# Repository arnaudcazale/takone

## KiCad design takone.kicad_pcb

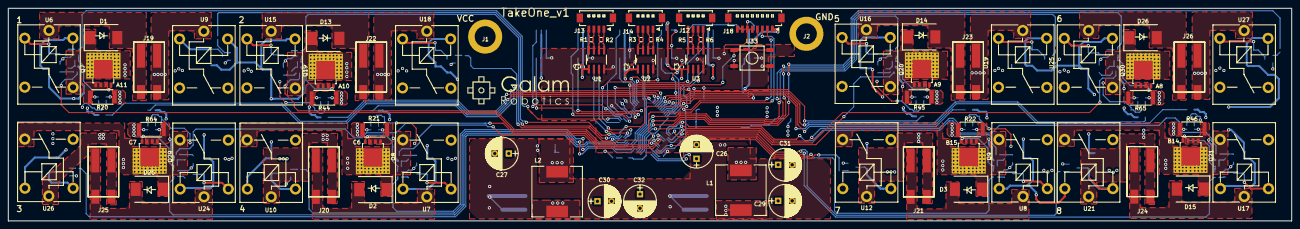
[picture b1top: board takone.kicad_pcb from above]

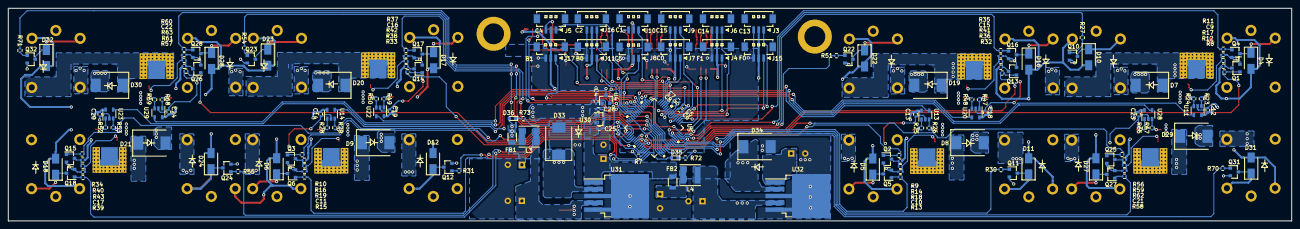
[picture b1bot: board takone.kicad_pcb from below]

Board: 4 copper layers, 320.0 x 53.0 mm, 238 parts (163 on the bottom side), 187 nets.

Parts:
C1, C2, C3, C6, C8, C12, C13, C14, C18, C19, C20, C23, C24, C25, C28: 100n; C_0402
C4: 0.47u; C_0402
C5: 1u; C_0402
C7: 4.7u; C_0402
C9, C10, C11, C15, C16, C17, C21, C22: DNP; C_0402
C26, C27, C31, C32: 100u; CP_Radial_D8.0mm_P3.50mm
C29, C30: 330u; CP_Radial_D8.0mm_P3.50mm
D1, D2, D3, D7, D8, D9, D13, D14, D15, D19, D20, D21, D25, D26, D29, D30: S10JC; D_SMC
D4, D5, D6, D10, D11, D12, D16, D17, D18, D22, D23, D24, D27, D28, D31, D32: M1; D_SMA
D33, D34: SS3H10; D_SMC
D35, D36: LED; LED_0603
FB1, FB2: Ferrite_Bead; R_1206
J1, J2: Conn_01x01; hole
J3, J4, J5, J6, J7, J8, J9, J10, J11, J15, J16, J17: Conn_01x03; Hirose_DF13C-03P-1.25V_03x1.25mm_Straight
J12, J13, J14: Conn_01x04; Hirose_DF13C-04P-1.25V_04x1.25mm_Straight
J18: Conn_01x08; Hirose_DF13C-08P-1.25V_08x1.25mm_Straight
J19, J20, J21, J22, J23, J24, J25, J26: Conn_02x02_Counter_Clockwise; P-2060-402998-404
L1: 220uH; L_12x12mm_h8mm
L2: 1mH; L_12x12mm_h8mm
L3, L4: 20u; L_Taiyo-Yuden_MD-5050
Q1, Q2, Q3, Q4, Q5, Q6, Q10, Q11, Q12, Q13, Q14, Q15, Q16, Q17, Q18, Q22, Q23, Q24, Q25, Q26, Q27, Q28, Q31, Q32: SS8050; SOT-23
Q7, Q8, Q9, Q19, Q20, Q21, Q29, Q30: PSMN028-100YS; LFPAK56_ThermalVias-1
R1, R2, R3, R4, R5, R6: 120; R_0402
R7, R12, R14, R16, R36, R38, R40, R59, R61: 10k; R_0402
R8, R9, R10, R11, R13, R15, R27, R30, R31, R32, R33, R34, R35, R37, R39, R51, R54, R55, R56, R57, R58, R60, R70, R71: 680R; R_0402
R17, R18, R19, R41, R42, R43, R62, R63: 1; R_0402
R20, R21, R22, R44, R45, R46, R64, R65: 0.05; R_2512
R23, R24, R25, R26, R28, R29, R47, R48, R49, R50, R52, R53, R66, R67, R68, R69: 0; R_0402
R72, R73: 330R; R_0402
U1, U2, U3: R_8; ADM3488ARZ
U4: REF2925; SOT-23
U5: LQFP-64; STM32G0_LQFP64_T1
U6, U7, U8, U9, U10, U12, U15, U16, U17, U18, U19, U21, U24, U25, U26, U27: Relay; Relay_SPDT_SANYOU_SRD_Series_Form_C
U11, U13, U14, U20, U22, U23, U28, U29: INA180; SOT-23-5
U30: TLV760; SOT-23
U31, U32: TL2575HV; TO-263-5_TabPin3
U33: switch

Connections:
+3.3V(ANALOG): C4.1, C12.2, C13.2, C14.2, C18.2, C19.2, C20.2, C23.2, C24.2, C28.1, U4.1, U11.5, U13.5, U14.5, U20.5, U22.5, U23.5, U28.5, U29.5, U30.1
+3.3V(DIG): C1.1, C2.1, C3.1, C7.1, C8.1, D36.2, FB1.1, J3.2, J4.2, J5.2, J6.2, J7.2, J8.2, J9.2, J10.2, J11.2, J15.2, J16.2, J17.2, J18.1, U1.1, U2.1, U3.1, U5.6, U5.8
+12V: C25.1, C26.1, D4.2, D5.2, D6.2, D10.2, D11.2, D12.2, D16.2, D17.2, D18.2, D22.2, D23.2, D24.2, D27.2, D28.2, D31.2, D32.2, FB2.1, R12.1, R14.1, R16.1, R36.1, R38.1, R40.1, R59.1, R61.1, U6.4, U7.4, U8.4, U9.4, U10.4, U12.4, U15.4, U16.4, U17.4, U18.4, U19.4, U21.4, U24.4, U25.4, U26.4, U27.4, U30.2, U31.1
+48V: C27.1, J1.1, U6.2, U7.2, U8.2, U9.2, U10.2, U12.2, U15.2, U16.2, U17.2, U18.2, U19.2, U21.2, U24.2, U25.2, U26.2, U27.2, U32.1
/command/NRST: J18.4, U5.12, U33.1, U33.2
/command/RX1: U1.2, U5.61
/command/RX2: U2.2, U5.56
/command/RX3: U3.2, U5.1
/command/SWCLK: J18.3, R7.1, U5.46
/command/SWDIO: J18.2, U5.45
/command/TX1: U1.3, U5.60
/command/TX2: U2.3, U5.55
/command/TX3: U3.3, U5.64
/command/encoder1: J3.1, U5.3
/command/encoder2: J6.1, U5.4
/command/encoder3: J9.1, U5.5
/command/encoder4: J15.1, U5.10
/command/encoder5: J4.1, U5.11
/command/encoder6: J7.1, U5.13
/command/encoder7: J10.1, U5.14
/command/encoder8: J16.1, U5.15
/command/spare1: J5.1, U5.25
/command/spare2: J8.1, U5.26
/command/spare3: J11.1, U5.27
/command/spare4: J17.1, U5.28
GND: C9.2, C10.2, C11.2, C15.2, C16.2, C17.2, C21.2, C22.2, C25.2, C26.2, C27.2, C28.2, C29.2, C30.2, C31.2, C32.2, D33.2, D34.2, Q1.2, Q2.2, Q3.2, Q4.2, Q5.2, Q6.2, Q10.2, Q11.2, Q12.2, Q13.2, Q14.2, Q15.2, Q16.2, Q17.2, Q18.2, Q22.2, Q23.2, Q24.2, Q25.2, Q26.2, Q27.2, Q28.2, Q31.2, Q32.2, R73.2, U30.3, U31.3, U31.5, U32.3, U32.5
GNDA: C12.1, C13.1, C14.1, C18.1, C19.1, C20.1, C23.1, C24.1, U11.2, U13.2, U14.2, U20.2, U22.2, U23.2, U28.2, U29.2
GNDD: C1.2, C2.2, C3.2, C4.2, C5.2, C6.2, C7.2, C8.2, J3.3, J4.3, J5.3, J6.3, J7.3, J8.3, J9.3, J10.3, J11.3, J15.3, J16.3, J17.3, J18.5, J18.6, J18.7, J18.8, R7.2, R72.2, U1.4, U2.4, U3.4, U4.3, U5.9, U33.3, U33.4
GNDPWR: R20.1, R21.1, R22.1, R24.1, R26.1, R29.1, R44.1, R45.1, R46.1, R48.1, R50.1, R53.1, R64.1, R65.1, R67.1, R69.1
MOS1: R8.1, U5.43
MOS2: R32.1, U5.42
MOS3: R56.1, U5.39
MOS4: R9.1, U5.38
MOS5: R33.1, U5.37
MOS6: R57.1, U5.36
MOS7: R10.1, U5.35
MOS8: R34.1, U5.34
unnamed: C5.1, C6.1, U4.2, U5.7
unnamed: C9.1, Q7.4, R17.2
unnamed: C10.1, Q8.4, R18.2
unnamed: C11.1, Q9.4, R19.2
unnamed: C15.1, Q19.4, R41.2
unnamed: C16.1, Q20.4, R42.2
unnamed: C17.1, Q21.4, R43.2
unnamed: C21.1, Q29.4, R62.2
unnamed: C22.1, Q30.4, R63.2
unnamed: C29.1, L1.2, L3.1, U31.4
unnamed: C30.1, L2.2, L4.1, U32.4
unnamed: C31.1, FB1.2, L3.2
unnamed: C32.1, FB2.2, L4.2
unnamed: D1.1, D7.1, Q7.5, U6.3, U9.3
unnamed: D1.2, J19.1, J19.2, U6.5
unnamed: D2.1, D8.1, Q8.5, U7.3, U10.3
unnamed: D2.2, J20.1, J20.2, U7.5
unnamed: D3.1, D9.1, Q9.5, U8.3, U12.3
unnamed: D3.2, J21.1, J21.2, U8.5
unnamed: D4.1, Q4.3, U6.1
unnamed: D5.1, Q5.3, U7.1
unnamed: D6.1, Q6.3, U8.1
unnamed: D7.2, J19.3, J19.4, U9.5
unnamed: D8.2, J20.3, J20.4, U10.5
unnamed: D9.2, J21.3, J21.4, U12.5
unnamed: D10.1, Q10.3, U9.1
unnamed: D11.1, Q11.3, U10.1
unnamed: D12.1, Q12.3, U12.1
unnamed: D13.1, D19.1, Q19.5, U15.3, U18.3
unnamed: D13.2, J22.1, J22.2, U15.5
unnamed: D14.1, D20.1, Q20.5, U16.3, U19.3
unnamed: D14.2, J23.1, J23.2, U16.5
unnamed: D15.1, D21.1, Q21.5, U17.3, U21.3
unnamed: D15.2, J24.1, J24.2, U17.5
unnamed: D16.1, Q16.3, U15.1
unnamed: D17.1, Q17.3, U16.1
unnamed: D18.1, Q18.3, U17.1
unnamed: D19.2, J22.3, J22.4, U18.5
unnamed: D20.2, J23.3, J23.4, U19.5
unnamed: D21.2, J24.3, J24.4, U21.5
unnamed: D22.1, Q22.3, U18.1
unnamed: D23.1, Q23.3, U19.1
unnamed: D24.1, Q24.3, U21.1
unnamed: D25.1, D29.1, Q29.5, U24.3, U26.3
unnamed: D25.2, J25.1, J25.2, U24.5
unnamed: D26.1, D30.1, Q30.5, U25.3, U27.3
unnamed: D26.2, J26.1, J26.2, U25.5
unnamed: D27.1, Q27.3, U24.1
unnamed: D28.1, Q28.3, U25.1
unnamed: D29.2, J25.3, J25.4, U26.5
unnamed: D30.2, J26.3, J26.4, U27.5
unnamed: D31.1, Q31.3, U26.1
unnamed: D32.1, Q32.3, U27.1
unnamed: D33.1, L1.1, U31.2
unnamed: D34.1, L2.1, U32.2
unnamed: D35.1, R72.1
unnamed: D35.2, U5.29
unnamed: D36.1, R73.1
unnamed: J12.1, R6.2, U3.5
unnamed: J12.2, R6.1, U3.6
unnamed: J12.3, R5.2, U3.7
unnamed: J12.4, R5.1, U3.8
unnamed: J13.1, R2.2, U1.5
unnamed: J13.2, R2.1, U1.6
unnamed: J13.3, R1.2, U1.7
unnamed: J13.4, R1.1, U1.8
unnamed: J14.1, R4.2, U2.5
unnamed: J14.2, R4.1, U2.6
unnamed: J14.3, R3.2, U2.7
unnamed: J14.4, R3.1, U2.8
unnamed: Q1.1, R8.2
unnamed: Q1.3, R12.2, R17.1
unnamed: Q2.1, R9.2
unnamed: Q2.3, R14.2, R18.1
unnamed: Q3.1, R10.2
unnamed: Q3.3, R16.2, R19.1
unnamed: Q4.1, R11.1
unnamed: Q5.1, R13.1
unnamed: Q6.1, R15.1
unnamed: Q7.1, Q7.2, Q7.3, R20.2, R23.1
unnamed: Q8.1, Q8.2, Q8.3, R21.2, R25.1
unnamed: Q9.1, Q9.2, Q9.3, R22.2, R28.1
unnamed: Q10.1, R27.1
unnamed: Q11.1, R30.1
unnamed: Q12.1, R31.1
unnamed: Q13.1, R32.2
unnamed: Q13.3, R36.2, R41.1
unnamed: Q14.1, R33.2
unnamed: Q14.3, R38.2, R42.1
unnamed: Q15.1, R34.2
unnamed: Q15.3, R40.2, R43.1
unnamed: Q16.1, R35.1
unnamed: Q17.1, R37.1
unnamed: Q18.1, R39.1
unnamed: Q19.1, Q19.2, Q19.3, R44.2, R47.1
unnamed: Q20.1, Q20.2, Q20.3, R45.2, R49.1
unnamed: Q21.1, Q21.2, Q21.3, R46.2, R52.1
unnamed: Q22.1, R51.1
unnamed: Q23.1, R54.1
unnamed: Q24.1, R55.1
unnamed: Q25.1, R56.2
unnamed: Q25.3, R59.2, R62.1
unnamed: Q26.1, R57.2
unnamed: Q26.3, R61.2, R63.1
unnamed: Q27.1, R58.1
unnamed: Q28.1, R60.1
unnamed: Q29.1, Q29.2, Q29.3, R64.2, R66.1
unnamed: Q30.1, Q30.2, Q30.3, R65.2, R68.1
unnamed: Q31.1, R70.1
unnamed: Q32.1, R71.1
unnamed: R23.2, U11.1
unnamed: R24.2, U11.3
unnamed: R25.2, U13.1
unnamed: R26.2, U13.3
unnamed: R28.2, U14.1
unnamed: R29.2, U14.3
unnamed: R47.2, U20.1
unnamed: R48.2, U20.3
unnamed: R49.2, U22.1
unnamed: R50.2, U22.3
unnamed: R52.2, U23.1
unnamed: R53.2, U23.3
unnamed: R66.2, U28.1
unnamed: R67.2, U28.3
unnamed: R68.2, U29.1
unnamed: R69.2, U29.3
RELAY1: R11.2, U5.2
RELAY2: R27.2, U5.63
RELAY3: R35.2, U5.62
RELAY4: R51.2, U5.59
RELAY5: R58.2, U5.58
RELAY6: R70.2, U5.57
RELAY7: R13.2, U5.54
RELAY8: R30.2, U5.53
RELAY9: R37.2, U5.52
RELAY10: R54.2, U5.51
RELAY11: R60.2, U5.50
RELAY12: R71.2, U5.49
RELAY13: R15.2, U5.48
RELAY14: R31.2, U5.47
RELAY15: R39.2, U5.44
RELAY16: R55.2, U5.33
SENSE1: U5.17, U11.4
SENSE2: U5.18, U20.4
SENSE3: U5.19, U28.4
SENSE4: U5.20, U13.4
SENSE5: U5.21, U22.4
SENSE6: U5.22, U29.4
SENSE7: U5.23, U14.4
SENSE8: U5.24, U23.4

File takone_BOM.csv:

Id;RÃ©fÃ©rence;BoÃ®tier;QuantitÃ©;DÃ©signation;Supplier;supplier part;Imax;Vmax;Pmax;commentaires;quantité (4 cartes);;LCSC;MOUSER;FUTURE ELECTRONICS
1;U18,U9,U6,U7,U8,U10,U12,U15,U16,U17,U19,U21,U24,U25,U26,U27;Relay_SPDT_SANYOU_SRD_Series_Form_C;16;Relay;LCSC;C30431;;;;;64;ok;22 articles;11 articles;1article
2;J19,J20,J21,J22,J23,J24,J25,J26;P-2060-402998-404;8;Conn_02x02_Counter_Clockwise;future electronics;;;;;;32;;;;
3;U33;switch;1;switch;LCSC;C83206;;;;;4;ok;;;
4;C29,C30;CP_Radial_D8.0mm_P3.50mm;2;330u;LCSC;C399165;;8V/20V;;;8;ok;;;
5;C31,C32,C26,C27;CP_Radial_D8.0mm_P3.50mm;4;100u;LCSC;C442932;;8V/20V/20V/60V;;;16;ok;;;
6;D1,D2,D3,D7,D8,D9,D13,D14,D15,D19,D20,D21,D25,D26,D29,D30;D_SMC;16;S10JC;LCSC;C382938;Imax moteur;> 48V;;;64;ok;;;
7;D4,D5,D6,D10,D11,D12,D16,D17,D18,D22,D23,D24,D27,D28,D31,D32;D_SMA;16;M1;LCSC;C181129;Imax relay;> 12V;;;64;ok;;;
8;D33,D34;D_SMC;2;SS3H10;LCSC;C467998;500mA/1A;20V/60V;;;8;ok;;;
9;J1,J2;hole;2;Conn_01x01;XXX;XXX;;;;;8;XXX;;;
10;J3,J4,J5,J6,J7,J8,J9,J10,J11,J15,J16,J17;Hirose_DF13C-03P-1.25V_03x1.25mm_Straight;12;Conn_01x03;LCSC;C52735;;;;;48;ok;;;
11;J12,J13,J14;Hirose_DF13C-04P-1.25V_04x1.25mm_Straight;3;Conn_01x04;LCSC;C47608;;;;;12;ok;;;
12;J18;Hirose_DF13C-08P-1.25V_08x1.25mm_Straight;1;Conn_01x08;LCSC;C53040;;;;;4;ok;;;
13;Q1,Q2,Q3,Q4,Q5,Q6,Q10,Q11,Q12,Q13,Q14,Q15,Q16,Q17,Q18,Q22,Q23,Q24,Q25,Q26,Q27,Q28,Q31,Q32;SOT-23;24;SS8050;LCSC;C181160;;;;;96;ok;;;
14;R20,R21,R22,R44,R45,R46,R64,R65;R_2512;8;0.02;LCSC;C105360;;;RI^2;;32;ok;;;
15;U1,U2,U3;ADM3488ARZ;3;R_8;MOUSER;584-ADM3488ARZ;;;;;12;ok;;;
16;U4;SOT-23;1;REF2925;LCSC;C81848;;;;;4;ok;;;
17;U5;STM32G070RBT6;1;LQFP-64;MOUSER;511-STM32G070RBT6;;;;;4;ok;;;
18;U11,U13,U14,U20,U22,U23,U28,U29;SOT-23-5;8;INA180;MOUSER;INA180B1QDBVRQ1;;;;;32;ok;;;
19;U30;SOT-23;1;TLV760;MOUSER;595-TLV76033DBZR;;;;;4;ok;;;
20;U31;TO-263-5_TabPin3;1;TL2575-33;MOUSER;595-TL2575-33IKTTR;;;;;4;ok;;;
21;U32;TO-263-5_TabPin3;1;TL2575HV-12;MOUSER;595-TL2575HV-12IKTTR;;;;;4;ok;;;
22;L1;12x12mm;1;220uH;MOUSER;673-P1170.224NLT;500mA;;;;4;ok;;;
23;L2;12x12mm;1;1mH;MOUSER;710-7447709102;1A;;;;4;ok;;;
24;L3,L4;5x5mm;2;20u;MOUSER;652-SRR4528A-220M;500mA/1A;;;;8;ok;;;
25;C1,C2,C3,C6,C8,C12,C13,C14,C18,C19,C20,C23,C24,C25,C28;C_0402;15;100n;LCSC;C169292;;8V;;;60;ok;;;
26;C4;C_0402;1;0.47u;LCSC;C338073;;8V;;;4;ok;;;
27;C5;C_0402;1;1u;LCSC;C307414;;8V;;;4;ok;;;
28;C7;C_0402;1;4.7u;LCSC;C342983;;8V;;;4;ok;;;
29;C9,C10,C11,C15,C16,C17,C21,C22;C_0402;8;DNP;XXX;XXX;;20V;;;32;XXX;;;
30;R1,R2,R3,R4,R5,R6;R_0402;6;120R;LCSC;C102779;;;0,063W ;;24;ok;;;
31;R7,R12,R14,R16,R36,R38,R40,R59,R61;R_0402;9;10k;LCSC;C327803;;;0,063W;;36;ok;;;
32;R8,R9,R10,R11,R13,R15,R27,R30,R31,R32,R33,R34,R35,R37,R39,R51,R54,R55,R56,R57,R58,R60,R70,R71;R_0402;24;3.9k;LCSC;C310259;;;0,063W;;96;ok;;;
33;R17,R18,R19,R41,R42,R43,R62,R63;R_0402;8;1R;LCSC;C168208;;;0,063W;;32;ok;;;
34;R23,R24,R25,R26,R28,R29,R47,R48,R49,R50,R52,R53,R66,R67,R68,R69;R_0402;16;0R;LCSC;C100568;;;0,063W;;64;ok;;;
35;Q7,Q8,Q9,Q19,Q20,Q21,Q29,Q30;LFPAK56_ThermalVias-1;8;PSMN028-100YS;MOUSER;771-PSMN028-100YS115;;;;;32;ok;;;
;LX?;12x12mm;1;680 uH;MOUSER;652-SRR1210A-681M;;;;bobine buck pour 36V;4;ok;;;
;FB2, FB1;1210;2;shunt/ferrite beads;MOUSER;855-S1731-46R;;;;;4;ok;;;
;R72, R73;R_0402;2;330R;LCSC;C427206;;;;;4;ok;;;
;D35, D36;D_0603;2;;LCSC;C72041;;;;;4;;;;

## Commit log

2020-04-10 ampli diff reference fix
2020-06-23 correctif empreintes

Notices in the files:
parts and their libraries:
Copyright 2016 Accelerated Designs. All rights reserved.
